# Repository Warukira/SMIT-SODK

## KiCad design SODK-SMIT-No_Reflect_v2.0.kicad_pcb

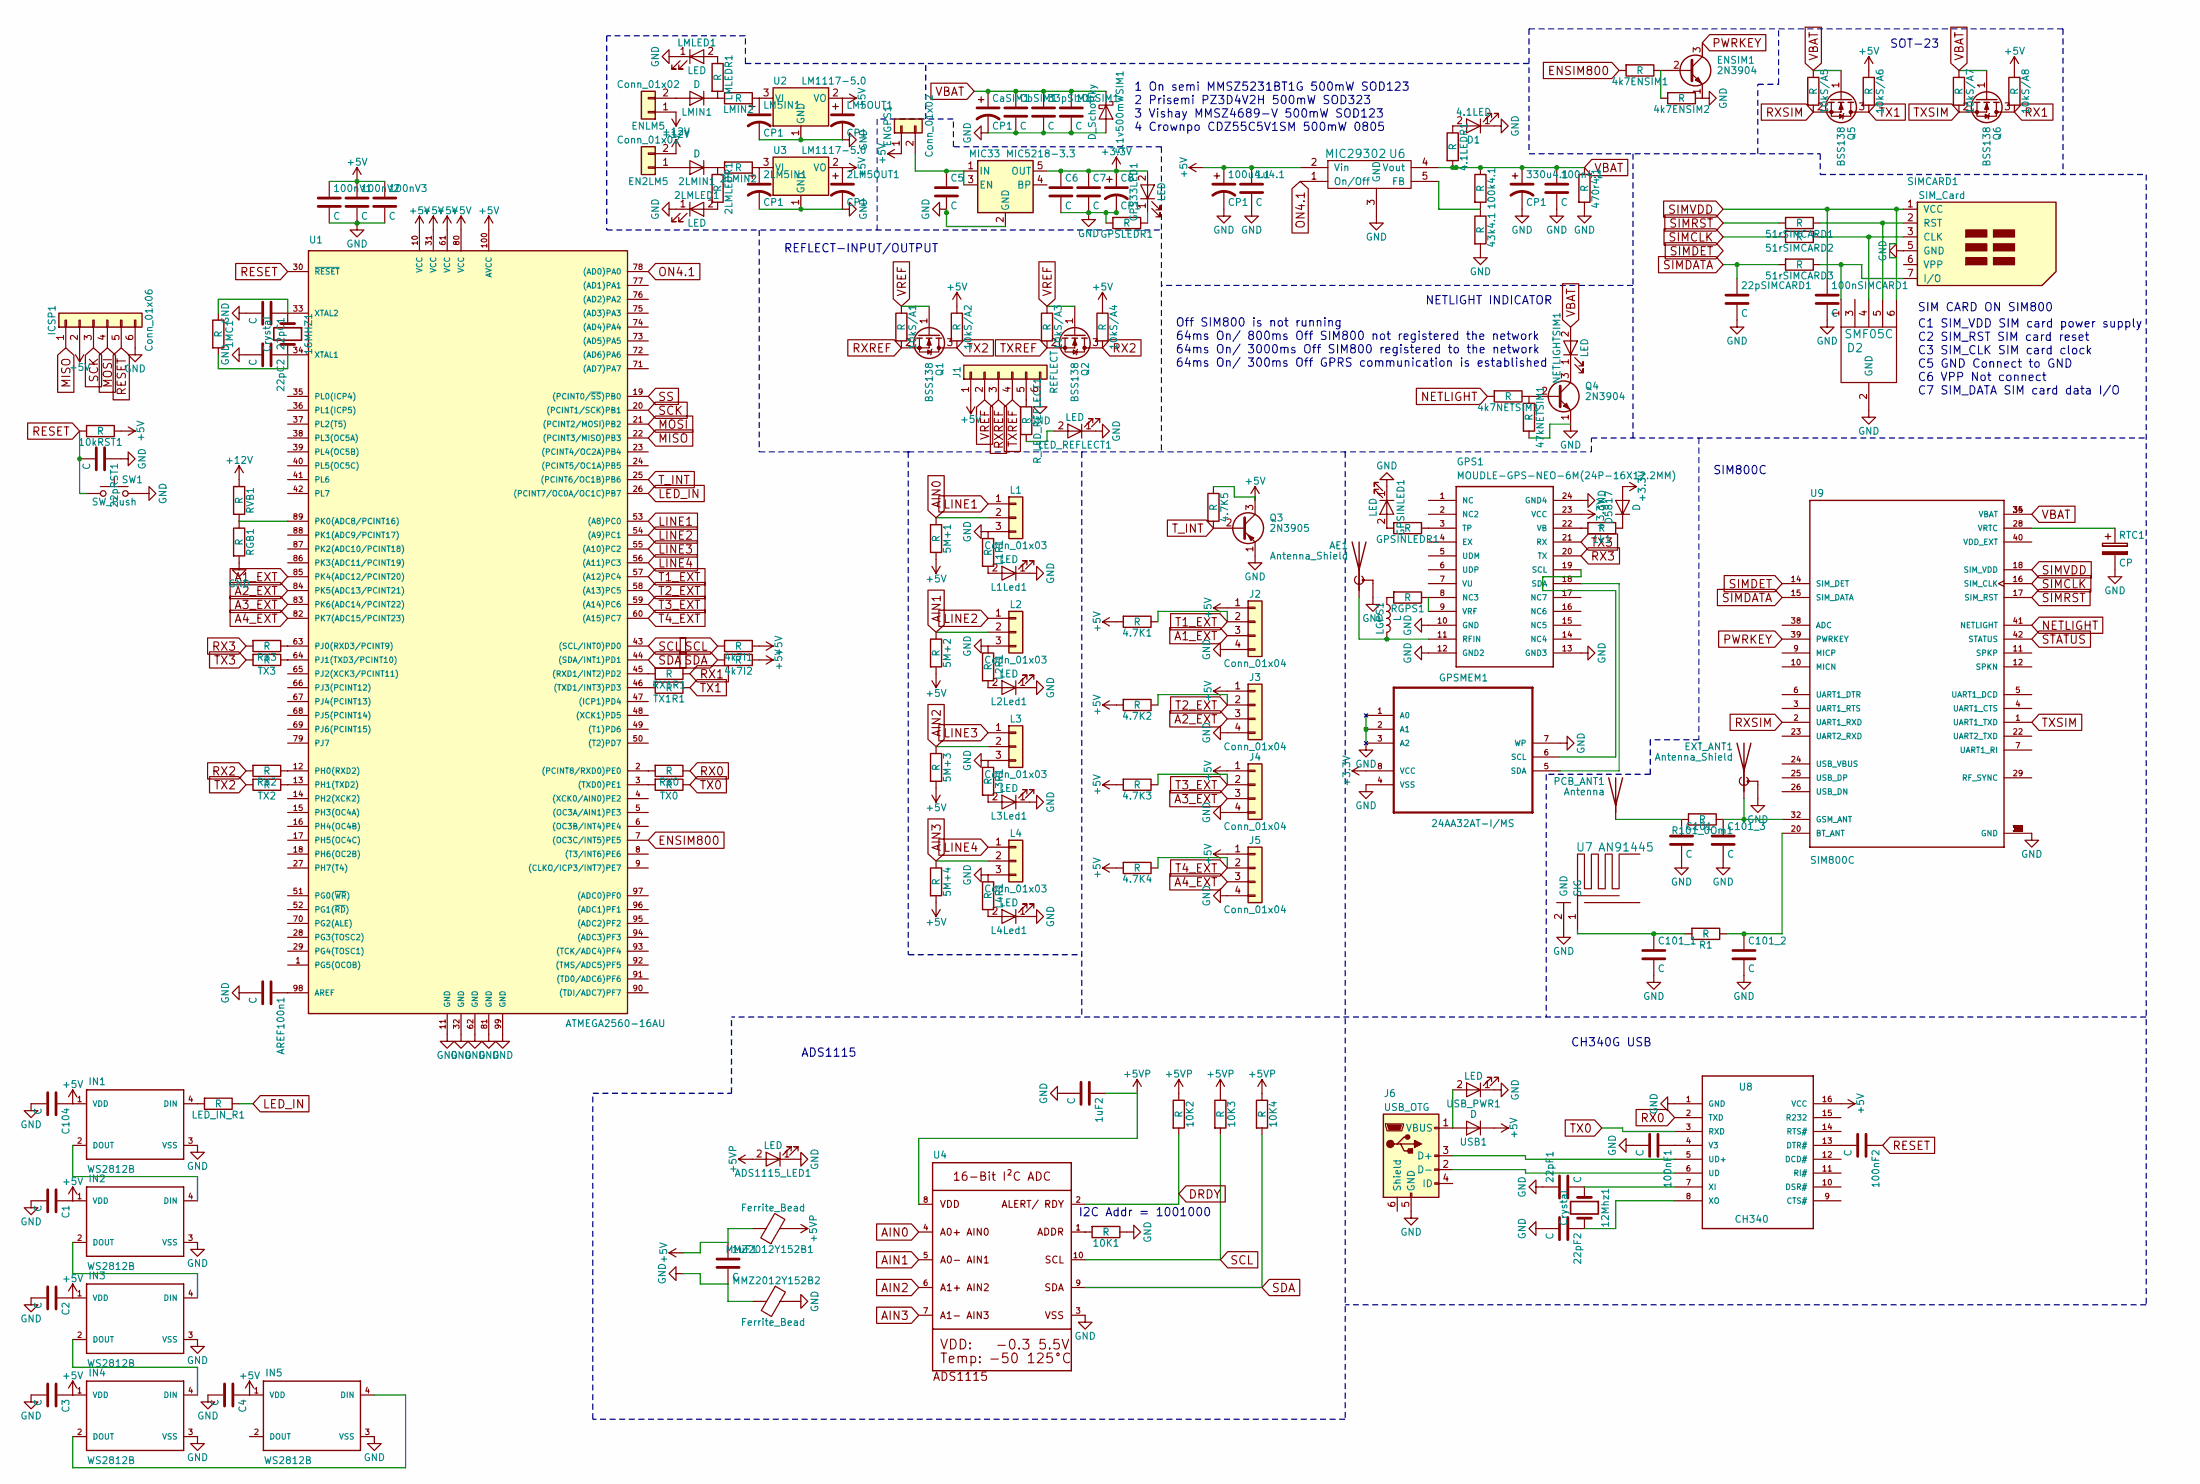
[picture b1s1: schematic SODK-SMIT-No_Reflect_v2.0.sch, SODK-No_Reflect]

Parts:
1MC1, 1k1, 2LMLEDR1, 4.1LEDR1, 4.7K1, 4.7K2, 4.7K3, 4.7K4, 4.7K5, 4k7ENSIM1, 4k7ENSIM2, 4k7I1, 4k7I2, 4k7NETSIM1, 5M+1, 5M+2, 5M+3, 5M+4, 10K1, 10K2, 10K3, 10K4, 10kRST1, 10kS/A1, 10kS/A2, 10kS/A3, 10kS/A4, 10kS/A5, 10kS/A6, 10kS/A7, 10kS/A8, 43k4.1, 47kNETSIM1, 51rSIMCARD1, 51rSIMCARD2, 51rSIMCARD3, 100k4.1, 470r4.1: R; R_0805
1u4.1, 1uF1, 1uF2, 10pSIM1, 22pC1, 22pC2, 22pF1, 22pF2, 22pRST1, 22pSIMCARD1, 33pSIM1, 100n4.1, 100nF1, 100nF2, 100nSIMCARD1, 100nV1, 100nV2, 100nV3: C; C_0805
2LM5IN1, 2LM5OUT1, 100u4.1, 330u4.1: CP1; CP_Radial_D5.0mm_P2.00mm
2LMIN1: D; D_1206
2LMIN2: R; R_0402
2LMLED1: LED; LED_0805
5.1v500mWSIM1: D_Schottky; D_SOD-123
12Mhz1, 16MHZ1: Crystal; Crystal_HC49-U_Vertical
ADS1115_LED1: LED; LED_0805
AE1: Antenna_Shield; SMB_Straight
AREF100n1: C; C_0805
C1, C2, C3, C4, C5, C6, C7, C101, C101_1, C101_2, C101_3, C104: C; C_0805
C8: CP1; CP_Radial_D5.0mm_P2.00mm
CaSIM1: CP1; CP_Radial_D5.0mm_P2.00mm
CbSIM1: C; C_0805
D1: 4.1LED; LED_0805
D2: SMF05C; SOT-363_SC-70-6_Handsoldering
D5817: D; D_DO-41_SOD81_P7.62mm_Horizontal
EN2LM5: Conn_01x02; Pin_Header_Straight_1x02_Pitch2.54mm
ENGPS1: Conn_01x02; Pin_Header_Straight_1x02_Pitch2.54mm
ENLM5: Conn_01x02; Pin_Header_Straight_1x02_Pitch2.54mm
ENSIM1: 2N3904; TO-92_Molded_Narrow
EXT_ANT1: Antenna_Shield; SMA_THT_Jack_Straight
GPS1: MOUDLE-GPS-NEO-6M(24P-16X12.2MM); GPS24P-SMD-1.1-16X12.2MM
GPS33LED1: LED; LED_0805
GPSINLED1: LED; LED_0805
GPSINLEDR1: R; R_0805
GPSLEDR1: R; R_0805
GPSMEM1: 24AA32AT-I/MS; SOP65P490X110-8N
ICSP1: Conn_01x06; Pin_Header_Straight_1x06_Pitch2.00mm
IN1, IN2, IN3, IN4, IN5: WS2812B
J1: REFLECT; Pin_Header_Straight_1x06_Pitch2.00mm
J2, J3, J4, J5: Conn_01x04; Pin_Header_Straight_1x04_Pitch2.00mm
J6: USB_OTG; USB_Micro-B_Wuerth-629105150521
L1, L2, L3, L4: Conn_01x03; Pin_Header_Straight_1x03_Pitch2.00mm
L1Led1, L2Led1, L3Led1, L4Led1: LED; LED_0805
L1R1, L2R1, L3R1, L4R1: R; R_0805
LED_IN_R1: R; R_0805
LED_REFLECT1: LED; LED_0805
LGPS1: L; L_1812
LM5IN1, LM5OUT1: CP1; CP_Radial_D5.0mm_P2.00mm
LMIN1: D; D_1206
LMIN2: R; R_0805
LMLED1: LED; LED_0805
LMLEDR1: R; R_0805
MIC33: MIC5218-3.3; SOT-23-5
MMZ2012Y152B1, MMZ2012Y152B2: Ferrite_Bead; L_0805
NETLIGHTSIM1: LED; LED_0805
PCB_ANT1: Antenna; Test_Point_Keystone_5015_Micro-Minature
Q1, Q2, Q5, Q6: BSS138; SOT-23
Q3: 2N3905; TO-92_Molded_Narrow
Q4: 2N3904; TO-92_Molded_Narrow
R1, R101_0Om1: R; R_0805
RGB1: R; R_0805
RGPS1: R; R_0805
RTC1: CP; CP_Radial_D5.0mm_P2.00mm
RVB1: R; R_0805
RX0, RX1R1, RX2, RX3: R; R_0805
R_LED_REFLECT1: R; R_0805
SIMCARD1: SIM_Card; ICC-313
SW1: SW_Push; SW_SPST_FSMSM
TX0, TX1R1, TX2, TX3: R; R_0805
U1: ATMEGA2560-16AU; TQFP-100_14x14mm_Pitch0.5mm
U2, U3: LM1117-5.0; SOT-223-3_TabPin2
U4: ADS1115; MSOP10
U6: MIC29302; TO-220-5_Horizontal
U7: AN91445
U8: CH340; SO16
U9: SIM800C; LCC110P1570X1760X250-42N
USB1: D; D_1206
USB_PWR1: LED; LED_0805

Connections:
+3V3: C6.1, C7.1, C8.1, D5817.2 (A), GPS1.23 (VCC), GPS33LED1.2 (A), GPSMEM1.8 (VCC), MIC33.5 (OUT)
+5V: 1u4.1.1, 1uF1.1, 2LM5OUT1.1, 4.7K1.2, 4.7K2.2, 4.7K3.2, 4.7K4.2, 4.7K5.1, 4k7I1.1, 4k7I2.1, 5M+1.2, 5M+2.2, 5M+3.2, 5M+4.2, 10kRST1.1, 10kS/A2.1, 10kS/A4.1, 10kS/A6.1, 10kS/A8.1, 100nV1.1, 100nV2.1, 100nV3.1, 100u4.1.1, C1.1, C2.1, C3.1, C4.1, C104.1, ENGPS1.1, ICSP1.2, IN1.1 (VDD), IN2.1 (VDD), IN3.1 (VDD), IN4.1 (VDD), IN5.1 (VDD), J1.1, J2.1, J3.1, J4.1, J5.1, LM5OUT1.1, MMZ2012Y152B1.1, Q3.3 (C), U1.10 (VCC), U1.31 (VCC), U1.61 (VCC), U1.80 (VCC), U1.100 (AVCC), U2.2 (VO), U3.2 (VO), U6.2 (Vin), U8.16 (VCC), USB1.1 (K)
+5VP: 1uF2.1, 10K2.1, 10K3.1, 10K4.1, ADS1115_LED1.2 (A), MMZ2012Y152B1.2, U4.8 (VDD)
+12V: EN2LM5.2, ENLM5.1, RVB1.1
A1_EXT: J2.3, U1.85 (PK4(ADC12/PCINT20))
A2_EXT: J3.3, U1.84 (PK5(ADC13/PCINT21))
A3_EXT: J4.3, U1.83 (PK6(ADC14/PCINT22))
A4_EXT: J5.3, U1.82 (PK7(ADC15/PCINT23))
AIN0: 5M+1.1, L1.2, U4.4 (AIN0)
AIN1: 5M+2.1, L2.2, U4.5 (AIN1)
AIN2: 5M+3.1, L3.2, U4.6 (AIN2)
AIN3: 5M+4.1, L4.2, U4.7 (AIN3)
DRDY: 10K2.2, U4.2 (ALERT/RDY)
ENSIM800: 4k7ENSIM1.2, U1.7 ((OC3C/INT5)PE5)
GND: 1u4.1.2, 1uF1.2, 1uF2.2, 2LM5IN1.2, 2LM5OUT1.2, 2LMLED1.1 (K), 4k7ENSIM2.1, 5.1v500mWSIM1.2 (A), 10K1.1, 10pSIM1.2, 22pC1.2, 22pC2.2, 22pF1.1, 22pF2.2, 22pRST1.1, 22pSIMCARD1.2, 33pSIM1.2, 43k4.1.2, 47kNETSIM1.2, 100n4.1.2, 100nF1.2, 100nSIMCARD1.2, 100nV1.2, 100nV2.2, 100nV3.2, 100u4.1.2, 330u4.1.2, 470r4.1.2, ADS1115_LED1.1 (K), AE1.2 (Shield), AREF100n1.2, C1.2, C2.2, C3.2, C4.2, C5.2, C6.2, C7.2, C8.2, C101.2, C101_1.2, C101_2.2, C101_3.2, C104.2, CaSIM1.2, CbSIM1.2, D1.1 (K), D2.2 (GND), ENSIM1.1 (E), EXT_ANT1.2 (Shield), GPS1.10 (GND), GPS1.12 (GND2), GPS1.13 (GND3), GPS1.24 (GND4), GPSINLED1.1 (K), GPSLEDR1.2, GPSMEM1.1 (A0), GPSMEM1.2 (A1), GPSMEM1.3 (A2), GPSMEM1.4 (VSS), GPSMEM1.7 (WP), ICSP1.6, IN1.3 (VSS), IN2.3 (VSS), IN3.3 (VSS), IN4.3 (VSS), IN5.3 (VSS), J1.6, J2.4, J3.4, J4.4, J5.4, J6.5 (GND), L1.3, L1Led1.1 (K), L1R1.1, L2.3, L2Led1.1 (K), L2R1.1, L3.3, L3Led1.1 (K), L3R1.1, L4.3, L4Led1.1 (K), L4R1.1, LED_REFLECT1.1 (K), LM5IN1.2, LM5OUT1.2, LMLED1.1 (K), MIC33.2 (GND), MMZ2012Y152B2.1, MMZ2012Y152B2.2, Q3.1 (E), Q4.1 (E), RGB1.2, RTC1.2, SIMCARD1.5 (GND), SW1.2, U1.11 (GND), U1.32 (GND), U1.62 (GND), U1.81 (GND), U1.99 (GND), U2.1 (GND), U3.1 (GND), U4.3 (VSS), U6.3 (GND), U7.2 (GND), U8.1 (GND), U9.8 (GND), U9.13 (GND), U9.19 (GND), U9.21 (GND), U9.27 (GND), U9.30 (GND), U9.31 (GND), U9.33 (GND), U9.36 (GND), U9.37 (GND), USB_PWR1.1 (K)
LED_IN: LED_IN_R1.1, U1.26 ((PCINT7/OC0A/OC1C)PB7)
LINE1: L1.1, U1.53 ((A8)PC0)
LINE2: L2.1, U1.54 ((A9)PC1)
LINE3: L3.1, U1.55 ((A10)PC2)
LINE4: L4.1, U1.56 ((A11)PC3)
MISO: ICSP1.1, U1.22 ((PCINT3/MISO)PB3)
MOSI: ICSP1.4, U1.21 ((PCINT2/MOSI)PB2)
NETLIGHT: 4k7NETSIM1.2, U9.41 (NETLIGHT)
unnamed: 1k1.1, D5817.1 (K)
unnamed: 1k1.2, GPS1.22 (VB)
unnamed: 2LM5IN1.1, 2LMIN2.1, U3.3 (VI)
unnamed: 2LMIN1.1 (K), 2LMIN2.2, 2LMLEDR1.1
unnamed: 2LMIN1.2 (A), EN2LM5.1
unnamed: 2LMLED1.2 (A), 2LMLEDR1.2
unnamed: 4.1LEDR1.1, D1.2 (A)
unnamed: 4k7ENSIM1.1, 4k7ENSIM2.2, ENSIM1.2 (B)
unnamed: 10K1.2, U4.1 (ADDR)
unnamed: 12Mhz1.1, 22pF1.2, U8.7 (XI)
unnamed: 12Mhz1.2, 22pF2.1, U8.8 (XO)
unnamed: 1MC1.1, 16MHZ1.1, 22pC1.1, U1.33 (XTAL2)
unnamed: 1MC1.2, 16MHZ1.2, 22pC2.1, U1.34 (XTAL1)
unnamed: 4k7NETSIM1.1, 47kNETSIM1.1, Q4.2 (B)
unnamed: 51rSIMCARD1.1, D2.5, SIMCARD1.2 (RST)
unnamed: 51rSIMCARD2.1, D2.4, SIMCARD1.3 (CLK)
unnamed: 51rSIMCARD3.1, D2.1, SIMCARD1.7 (I/O)
unnamed: 43k4.1.1, 100k4.1.2, U6.5 (FB)
unnamed: 100nF1.1, U8.4 (V3)
unnamed: 100nF2.2, U8.13 (DTR#)
unnamed: AE1.1 (A), GPS1.11 (RFIN), LGPS1.2
unnamed: AREF100n1.1, U1.98 (AREF)
unnamed: C5.1, ENGPS1.2, MIC33.1 (IN), MIC33.3 (EN)
unnamed: C101.1, PCB_ANT1.1, R101_0Om1.2
unnamed: C101_1.1, R1.2, U7.1 (SIG)
unnamed: C101_2.1, R1.1, U9.20 (BT_ANT)
unnamed: C101_3.1, EXT_ANT1.1 (A), R101_0Om1.1, U9.32 (GSM_ANT)
unnamed: ENLM5.2, LMIN1.2 (A)
unnamed: GPS1.3 (TP), GPSINLEDR1.1
unnamed: GPS1.8 (NC3), GPS1.9 (VRF), RGPS1.1
unnamed: GPS1.18 (SDA), GPSMEM1.5 (SDA)
unnamed: GPS1.19 (SCL), GPSMEM1.6 (SCL)
unnamed: GPS33LED1.1 (K), GPSLEDR1.1
unnamed: GPSINLED1.2 (A), GPSINLEDR1.2
unnamed: IN1.2 (DOUT), IN2.4 (DIN)
unnamed: IN1.4 (DIN), LED_IN_R1.2
unnamed: IN2.2 (DOUT), IN3.4 (DIN)
unnamed: IN3.2 (DOUT), IN4.4 (DIN)
unnamed: IN4.2 (DOUT), IN5.4 (DIN)
unnamed: J1.5, R_LED_REFLECT1.1
unnamed: J6.1 (VBUS), USB1.2 (A), USB_PWR1.2 (A)
unnamed: J6.2 (D-), U8.6 (UD)
unnamed: J6.3 (D+), U8.5 (UD+)
unnamed: L1Led1.2 (A), L1R1.2
unnamed: L2Led1.2 (A), L2R1.2
unnamed: L3Led1.2 (A), L3R1.2
unnamed: L4Led1.2 (A), L4R1.2
unnamed: LED_REFLECT1.2 (A), R_LED_REFLECT1.2
unnamed: LGPS1.1, RGPS1.2
unnamed: LM5IN1.1, LMIN2.1, U2.3 (VI)
unnamed: LMIN1.1 (K), LMIN2.2, LMLEDR1.2
unnamed: LMLED1.2 (A), LMLEDR1.1
unnamed: NETLIGHTSIM1.1 (K), Q4.3 (C)
unnamed: RGB1.1, RVB1.2, U1.89 (PK0(ADC8/PCINT16))
unnamed: RTC1.1, U9.28 (VRTC)
unnamed: RX0.2, U1.2 ((PCINT8/RXD0)PE0)
unnamed: RX1R1.2, U1.45 ((RXD1/INT2)PD2)
unnamed: RX2.1, U1.12 (PH0(RXD2))
unnamed: RX3.1, U1.63 (PJ0(RXD3/PCINT9))
unnamed: TX0.2, U1.3 ((TXD0)PE1)
unnamed: TX1R1.2, U1.46 ((TXD1/INT3)PD3)
unnamed: TX2.1, U1.13 (PH1(TXD2))
unnamed: TX3.1, U1.64 (PJ1(TXD3/PCINT10))
ON4.1: U1.78 ((AD0)PA0), U6.1 (On/Off)
PWRKEY: ENSIM1.3 (C), U9.39 (PWRKEY)
RESET: 10kRST1.2, 22pRST1.2, 100nF2.1, ICSP1.5, SW1.1, U1.30 (~RESET)
RX0: RX0.1, U8.2 (TXD)
RX1: 10kS/A8.2, Q6.3 (D), RX1R1.1
RX2: 10kS/A4.2, Q2.3 (D), RX2.2
RX3: GPS1.20 (TX), RX3.2
RXREF: 10kS/A1.2, J1.3, Q1.2 (S)
RXSIM: 10kS/A5.2, Q5.2 (S), U9.2 (UART1_RXD)
SCK: ICSP1.3, U1.20 ((PCINT1/SCK)PB1)
SCL: 4k7I1.2, 10K3.2, U1.43 ((SCL/INT0)PD0), U4.10 (SCL)
SDA: 4k7I2.2, 10K4.2, U1.44 ((SDA/INT1)PD1), U4.9 (SDA)
SIMCLK: 51rSIMCARD2.2, U9.16 (SIM_CLK)
SIMDATA: 22pSIMCARD1.1, 51rSIMCARD3.2, U9.15 (SIM_DATA)
SIMDET: U9.14 (SIM_DET)
SIMRST: 51rSIMCARD1.2, U9.17 (SIM_RST)
SIMVDD: 100nSIMCARD1.1, D2.6, SIMCARD1.1 (VCC), U9.18 (SIM_VDD)
SS: U1.19 ((PCINT0/~SS~)PB0)
STATUS: U9.42 (STATUS)
T1_EXT: 4.7K1.1, J2.2, U1.57 ((A12)PC4)
T2_EXT: 4.7K2.1, J3.2, U1.58 ((A13)PC5)
T3_EXT: 4.7K3.1, J4.2, U1.59 ((A14)PC6)
T4_EXT: 4.7K4.1, J5.2, U1.60 ((A15)PC7)
TX0: TX0.1, U8.3 (RXD)
TX1: 10kS/A6.2, Q5.3 (D), TX1R1.1
TX2: 10kS/A2.2, Q1.3 (D), TX2.2
TX3: GPS1.21 (RX), TX3.2
TXREF: 10kS/A3.2, J1.4, Q2.2 (S)
TXSIM: 10kS/A7.2, Q6.2 (S), U9.1 (UART1_TXD)
T_INT: 4.7K5.2, Q3.2 (B), U1.25 ((PCINT6/OC1B)PB6)
VBAT: 4.1LEDR1.2, 5.1v500mWSIM1.1 (K), 10kS/A5.1, 10kS/A7.1, 10pSIM1.1, 33pSIM1.1, 100k4.1.1, 100n4.1.1, 330u4.1.1, 470r4.1.1, CaSIM1.1, CbSIM1.1, NETLIGHTSIM1.2 (A), Q5.1 (G), Q6.1 (G), U6.4 (Vout), U9.34 (VBAT), U9.35 (VBAT)
VREF: 10kS/A1.1, 10kS/A3.1, J1.2, Q1.1 (G), Q2.1 (G)

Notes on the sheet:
1 On semi MMSZ5231BT1G 500mW SOD123 2 Prisemi PZ3D4V2H 500mW SOD323 3 Vishay MMSZ4689-V 500mW SOD123 4 Crownpo CDZ55C5V1SM 500mW 0805
SOT-23
SIM CARD ON SIM800
C1 SIM_VDD SIM card power supply C2 SIM_RST SIM card reset C3 SIM_CLK SIM card clock C5 GND Connect to GND C6 VPP Not connect C7 SIM_DATA SIM card data I/O
NETLIGHT INDICATOR
Off SIM800 is not running 64ms On/ 800ms Off SIM800 not registered the network 64ms On/ 3000ms Off SIM800 registered to the network 64ms On/ 300ms Off GPRS communication is established
SIM800C
I2C Addr = 1001000
ADS1115
CH340G USB
REFLECT-INPUT/OUTPUT

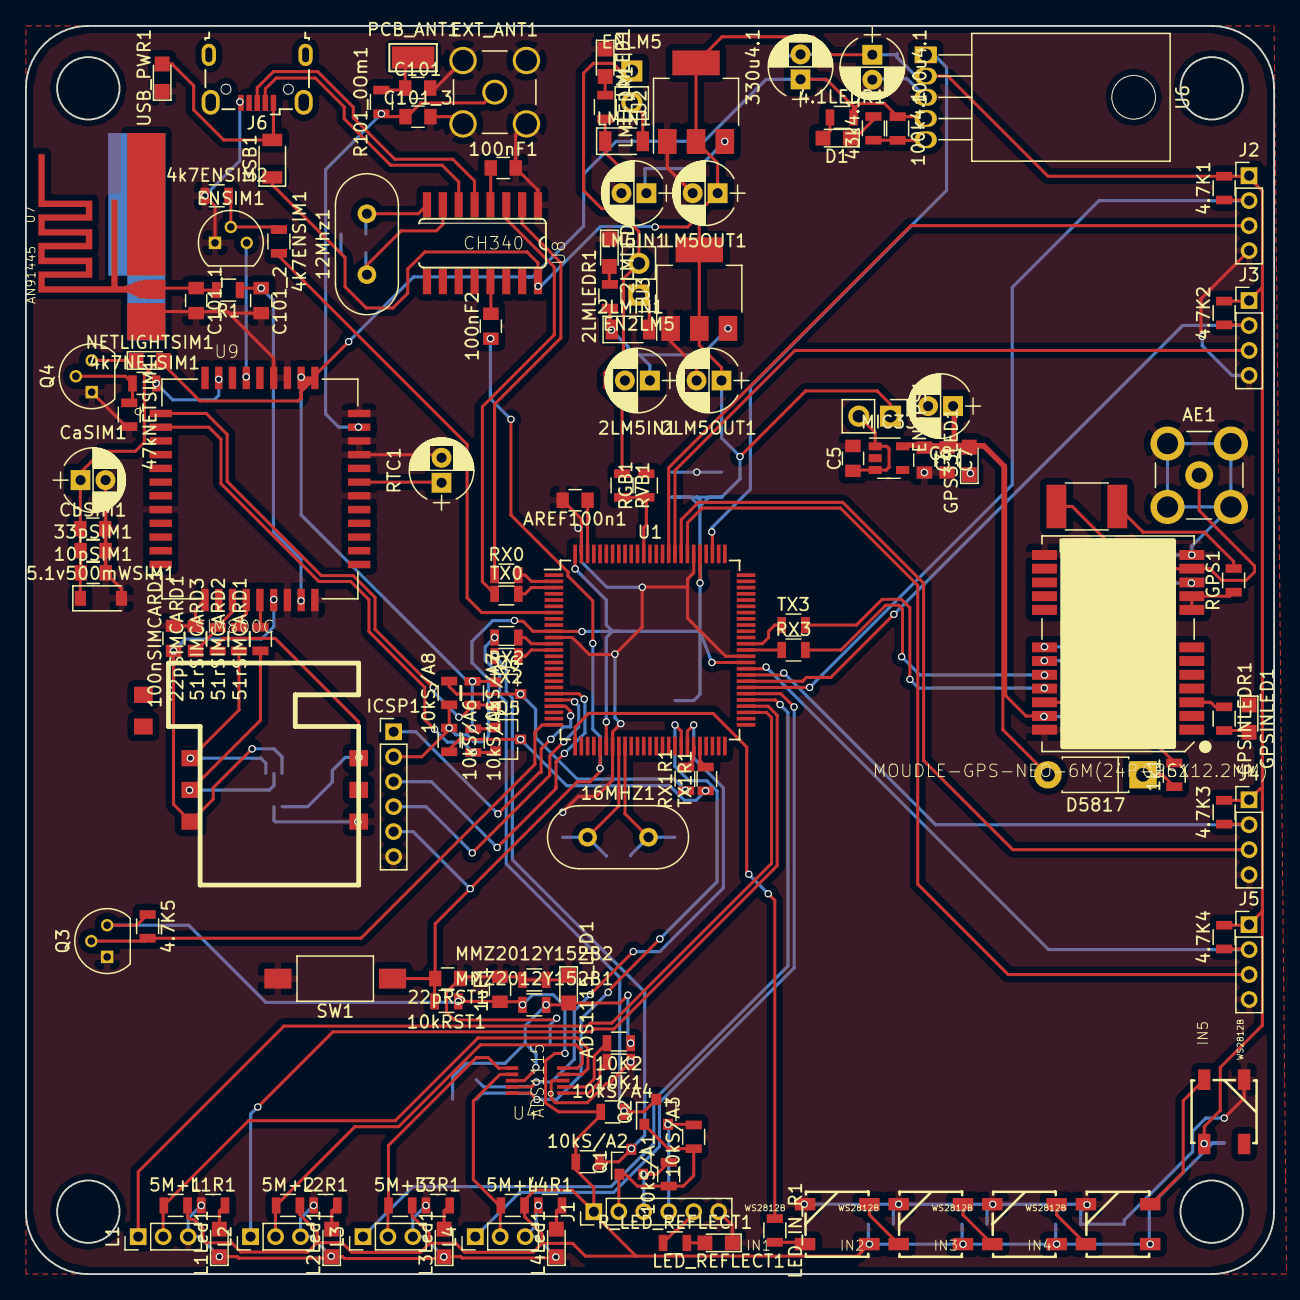
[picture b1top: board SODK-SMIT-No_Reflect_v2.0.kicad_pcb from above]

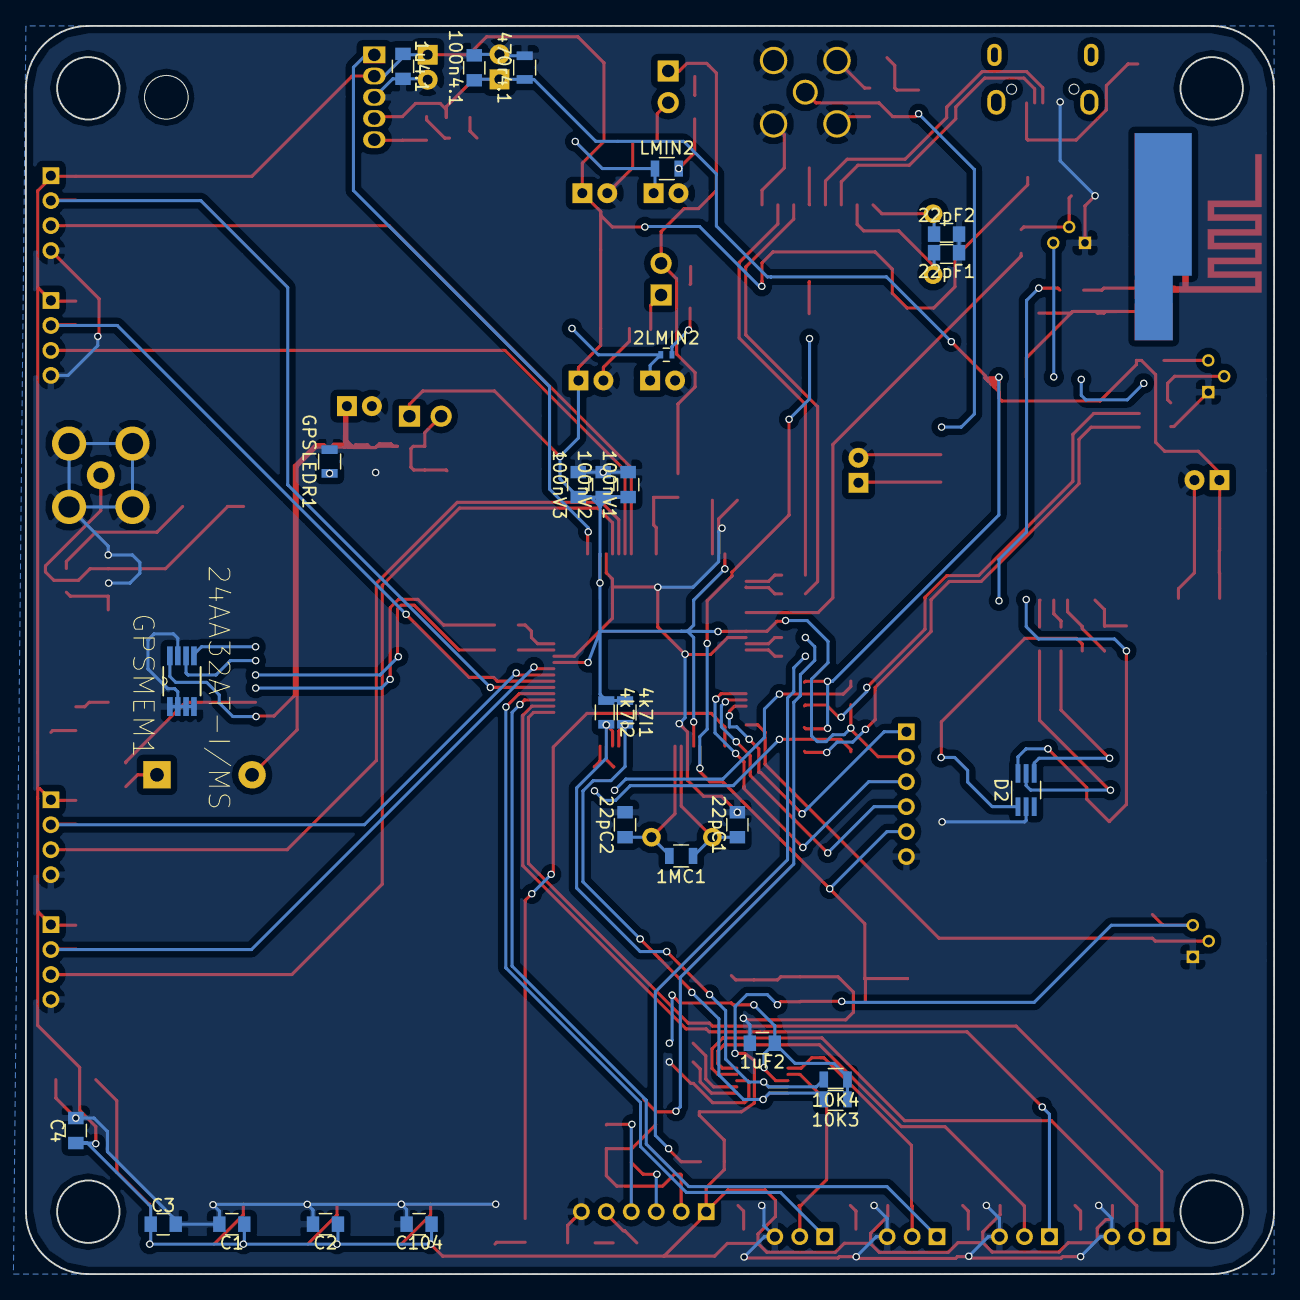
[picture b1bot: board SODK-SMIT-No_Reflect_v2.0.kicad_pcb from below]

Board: 2 copper layers, 100.0 x 100.0 mm, 169 parts (26 on the bottom side), 115 nets.
